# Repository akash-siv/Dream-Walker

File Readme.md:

# Low-Cost Wearable Solution for Mitigating VR Motion Sickness

## Project Summary
This project presents a low-cost wearable leg device leveraging embedded Tiny Machine Learning (TinyML) to mitigate Virtual Reality (VR) motion sickness by enabling standing-based locomotion control.

## Main Contributions
- Custom IMU dataset collected from 4 participants.
- Preprocessing using frequency-domain (FFT) and statistical feature extraction.
- Lightweight Deep Neural Network (DNN) trained and optimized for microcontroller deployment.
- End-to-end system achieving ~85% macro F1 score with under 100ms latency.
- Custom SteamVR driver integration with Bluetooth HID communication.

Authors:
--------
- Dhanush Balamurali (dhanushbalamurali@trentu.ca)
- Akash Sivasubramanian (akashsivasubramanian@trentu.ca)

Submission:
-----------
- This work is submitted as part of the AMOD Artificial Intelligence Project at Trent University, Peterborough, Canada.
- Submission includes all code, dataset, report, and driver files as required.

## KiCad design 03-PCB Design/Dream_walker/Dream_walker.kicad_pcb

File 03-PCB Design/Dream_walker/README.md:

# Dream_walker
 Locamotion controller for Steam VR games

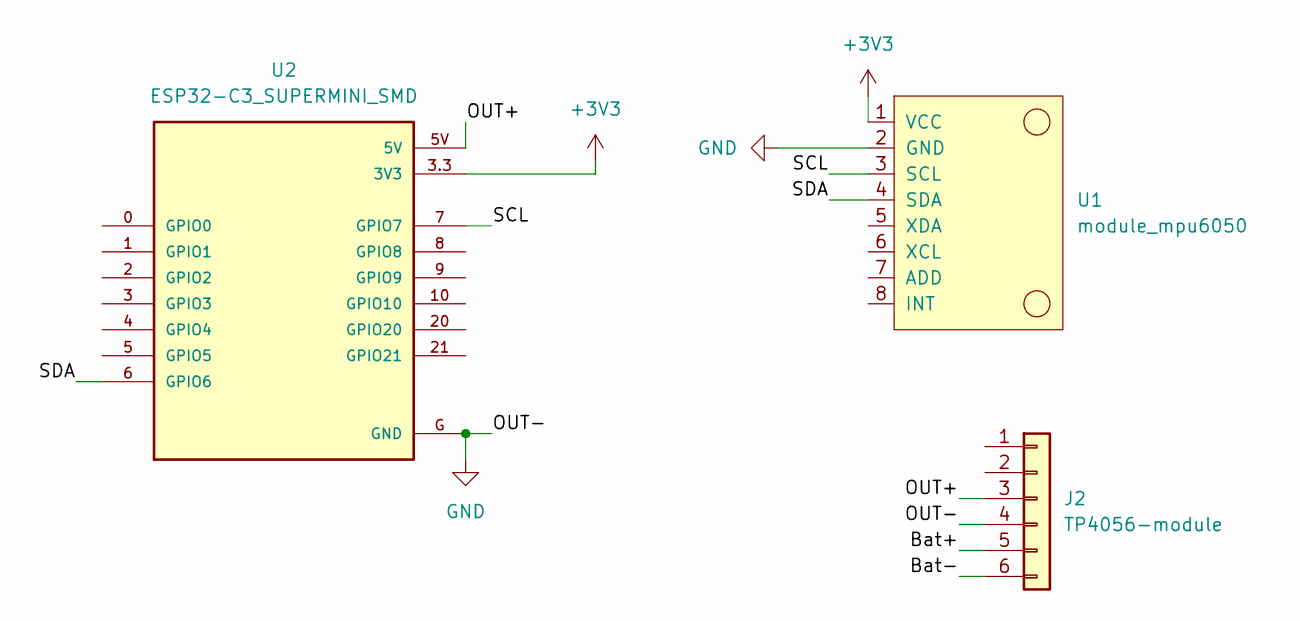
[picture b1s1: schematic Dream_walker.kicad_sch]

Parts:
J2: TP4056-module; tp4056-module
U1: module_mpu6050
U2: ESP32-C3_SUPERMINI_SMD; MODULE_ESP32-C3_SUPERMINI

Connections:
+3V3: U1.1 (VCC), U2.3.3 (3V3)
/Bat+: J2.5
/Bat-: J2.6
/OUT+: J2.3, U2.5V
/SCL: U1.3 (SCL), U2.7 (GPIO7)
/SDA: U1.4 (SDA), U2.6 (GPIO6)
GND: J2.4, U1.2 (GND), U2.G (GND)

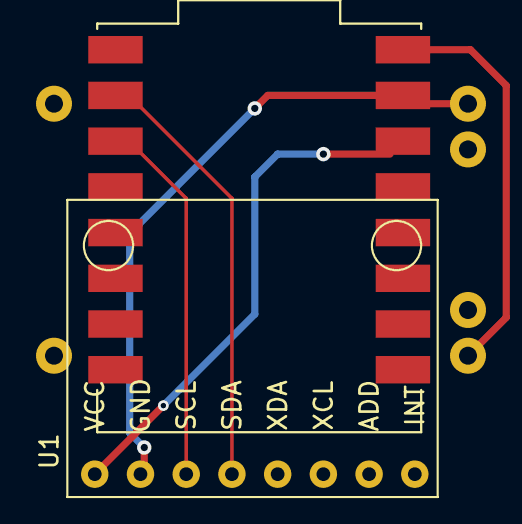
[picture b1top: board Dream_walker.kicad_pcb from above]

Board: 2 copper layers, 3 parts (1 on the bottom side), 5 nets.

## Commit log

2025-04-20 code organized
2025-04-20 Readme.md
2025-04-21 Update README.md of open vr frimware
2025-04-21 added additional frimware files
2025-04-21 added pcb files
2026-02-06 added rtos-queue
2026-05-18 Update Readme.md with video link
2026-05-18 distributed data collection and processing added
